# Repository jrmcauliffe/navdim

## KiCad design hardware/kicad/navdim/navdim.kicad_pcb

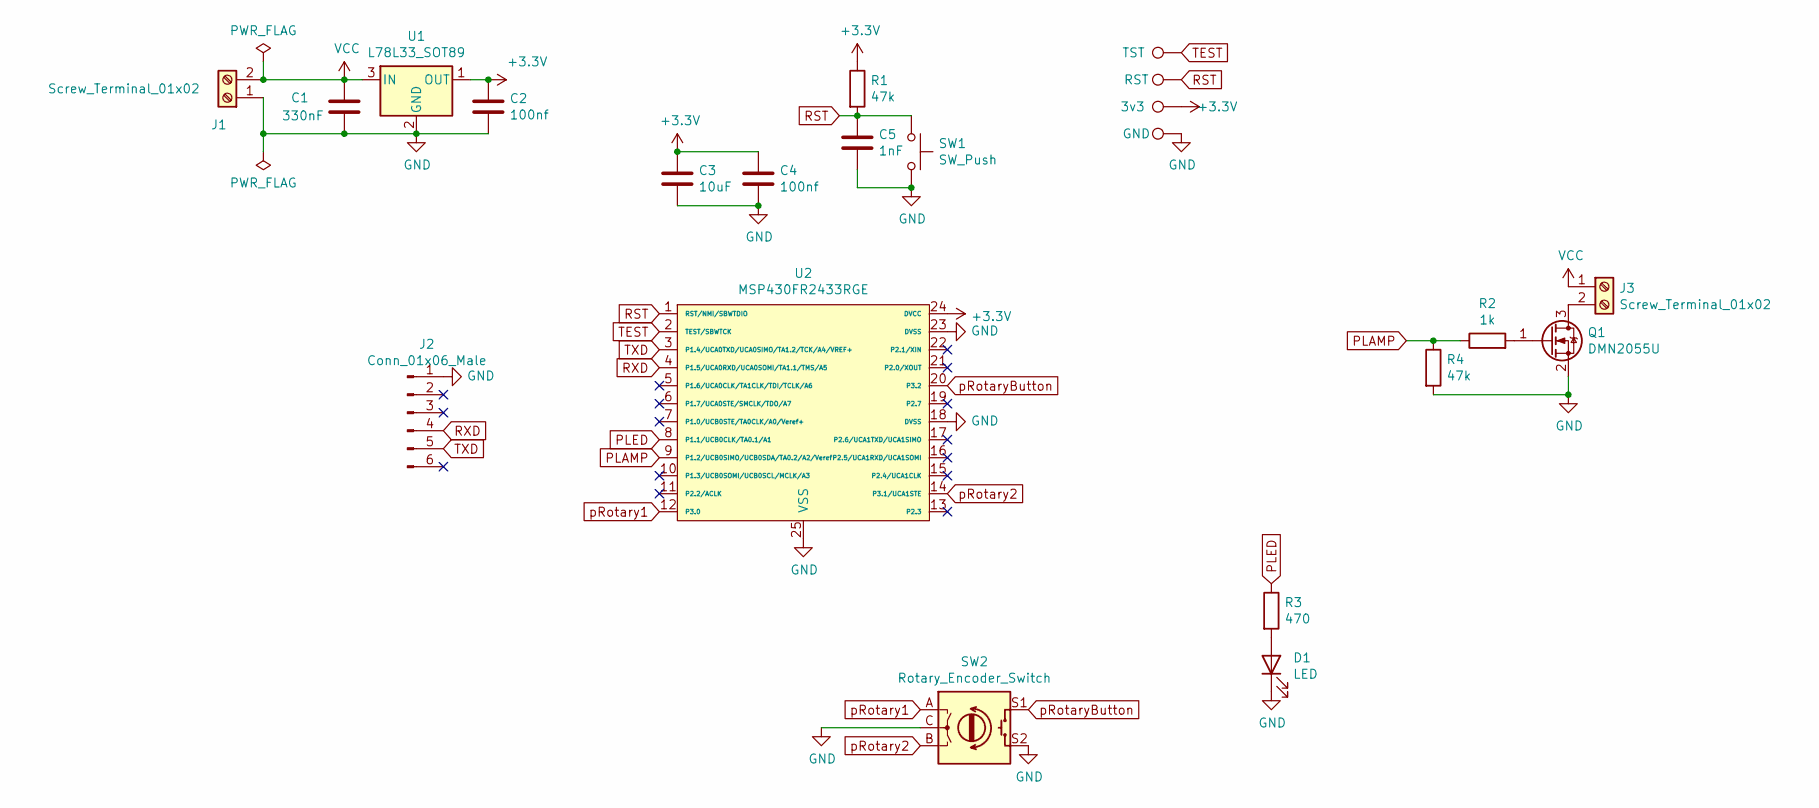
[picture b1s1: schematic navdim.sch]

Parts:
3v3: TestPoint; TestPoint_Pad_D1.5mm
C1: 330nF; C_0603_1608Metric_Pad1.05x0.95mm_HandSolder
C2, C4: 100nf; C_0603_1608Metric_Pad1.05x0.95mm_HandSolder
C3: 10uF; C_0603_1608Metric_Pad1.05x0.95mm_HandSolder
C5: 1nF; C_0603_1608Metric_Pad1.05x0.95mm_HandSolder
D1: LED; LED_0805_2012Metric_Pad1.15x1.40mm_HandSolder
GND: TestPoint; TestPoint_Pad_D1.5mm
J1, J3: Screw_Terminal_01x02; TerminalBlock_MetzConnect_Type059_RT06302HBWC_1x02_P3.50mm_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
J2: Conn_01x06_Male; PinHeader_1x06_P2.54mm_Vertical
Q1: DMN2055U; SOT-23
R1, R4: 47k; R_0603_1608Metric_Pad1.05x0.95mm_HandSolder
R2: 1k; R_0603_1608Metric_Pad1.05x0.95mm_HandSolder
R3: 470; R_0603_1608Metric_Pad1.05x0.95mm_HandSolder
RST: TestPoint; TestPoint_Pad_D1.5mm
SW1: SW_Push; SW_PUSH_6mm_H5mm
SW2: Rotary_Encoder_Switch; RotaryEncoder_Alps_EC12E-Switch_Vertical_H20mm
TST: TestPoint; TestPoint_Pad_D1.5mm
U1: L78L33_SOT89; SOT-89-3
U2: MSP430FR2433RGE; VQFN-24-1EP_4x4mm_P0.5mm_EP2.45x2.45mm

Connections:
+3V3: 3v3.1, C2.1, C3.1, C4.1, R1.1, U1.1 (OUT), U2.24 (DVCC)
GND: C1.2, C2.2, C3.2, C4.2, C5.2, D1.1 (K), GND.1, J1.1, J2.1, Q1.2 (S), R4.2, SW1.2, SW2.C, SW2.S2, U1.2 (GND), U2.18 (DVSS), U2.23 (DVSS), U2.25 (VSS)
unnamed: D1.2 (A), R3.2
unnamed: J3.2, Q1.3 (D)
unnamed: Q1.1 (G), R2.2
PLAMP: R2.1, R4.1, U2.9 (P1.2/UCB0SIMO/UCB0SDA/TA0.2/A2/Veref)
PLED: R3.1, U2.8 (P1.1/UCB0CLK/TA0.1/A1)
RST: C5.1, R1.2, RST.1, SW1.1, U2.1 (RST/NMI/SBWTDIO)
RXD: J2.4, U2.4 (P1.5/UCA0RXD/UCA0SOMI/TA1.1/TMS/A5)
TEST: TST.1, U2.2 (TEST/SBWTCK)
TXD: J2.5, U2.3 (P1.4/UCA0TXD/UCA0SIMO/TA1.2/TCK/A4/VREF+)
VCC: C1.1, J1.2, J3.1, U1.3 (IN)
pRotary1: SW2.A, U2.12 (P3.0)
pRotary2: SW2.B, U2.14 (P3.1/UCA1STE)
pRotaryButton: SW2.S1, U2.20 (P3.2)

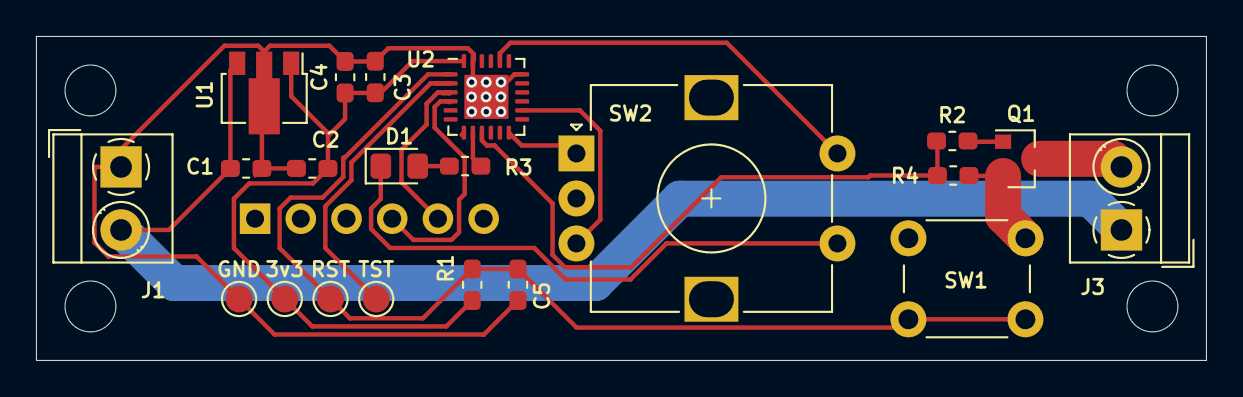
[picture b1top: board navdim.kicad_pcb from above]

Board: 2 copper layers, 65.0 x 18.0 mm, 22 parts (1 on the bottom side), 15 nets.

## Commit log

2021-10-19 Initial hardware desgin WIP
2021-10-20 Basic PCB layout
